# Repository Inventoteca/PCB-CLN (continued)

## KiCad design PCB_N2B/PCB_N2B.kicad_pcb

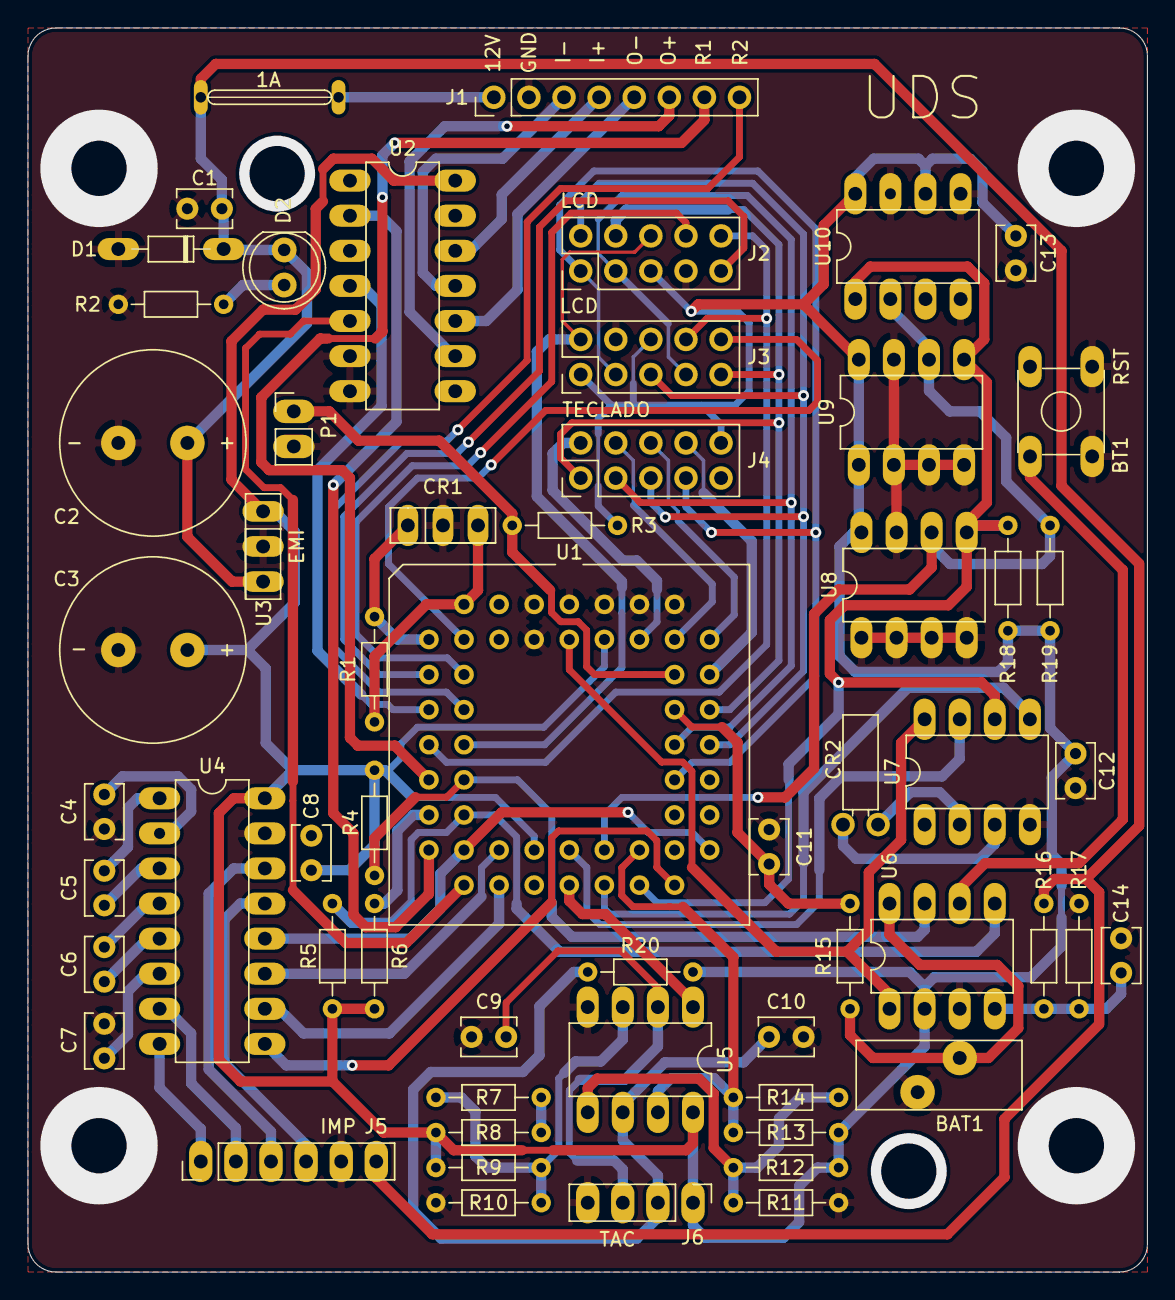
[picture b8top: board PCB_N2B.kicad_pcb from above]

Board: 2 copper layers, 81.0 x 90.0 mm, 58 parts (0 on the bottom side), 71 nets.

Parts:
1A1: Fuse; FUSE_10mm
BAT1: Battery_Cell; BatteryHolder_5.5_5mm
BT1: RST; SW_TH_Tactile_Omron_B3F-10xx
C1, C8, C9, C10, C11, C12, C13, C14: 10nF; C_Disc_D3.8mm_W2.6mm_P2.50mm
C2: 0.22F; CP_13.25_5.0mm
C3: na; CP_13.25_5.0mm
C4, C5, C6, C7: 2,2uF; C_Disc_D3.8mm_W2.6mm_P2.50mm
CR1: 800G137; Crystal_PIN-3
CR2: na; crystal_2.54_8.7mm
D1: na; D_DO-34_SOD68_P7.62mm_Horizontal
D2: RED; LED_D5.0mm_IRBlack
J1: Conn_01x08; PinHeader_1x08_P2.54mm_Vertical
J2, J3: LCD; PinHeader_2x05_P2.54mm_Vertical
J4: Teclado; PinHeader_2x05_P2.54mm_Vertical
J5: IMP; PinHeader_1x06_P2.54mm_Vertical
J6: TAC; PinHeader_1x04_P2.54mm_Vertical
P1: Conn_01x02; PinHeader_1x02_P2.54mm_Vertical
R1, R2, R3, R4, R5, R6, R7, R8, R9, R10, R11, R12, R13, R14, R15, R16, R17, R18, R19, R20: na; R_Axial_DIN0204_L3.6mm_D1.6mm_P7.62mm_Horizontal
U1: 68HC11_PLCC; PLCC-52_THT-Socket
U2: na; DIP-14_W7.62mm
U3: na; Crystal_PIN-3
U4: na; DIP-16_W7.62mm
U5, U6, U7, U8, U9, U10: na; DIP-8_W7.62mm

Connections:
Earth: BAT1.2, BT1.1, BT1.2, C1.2, C2.2, C3.2, C4.1, C7.1, C9.1, C10.2, C11.1, C12.1, C13.1, C14.1, CR1.2, D1.2, J1.2, J2.4, J3.7, J5.5, J6.4, P1.2, R2.1, R10.1, R11.2, R17.1, U1.1, U1.3, U1.4, U1.47, U1.49, U1.51, U2.3, U2.6, U2.7, U3.2, U4.15, U5.4, U6.3, U7.4, U8.1, U8.2, U8.3, U8.4, U8.7, U9.2, U9.3, U9.4, U9.7, U10.4, U10.5, U10.7
unnamed: C1.1, C2.1, D1.1, D2.1, U3.3
unnamed: 1A1.2, J1.1
unnamed: BT1.4, U6.6
unnamed: C9.2, U5.2
unnamed: C10.1, J6.2, R20.1, U5.6
unnamed: C11.2, R15.2, U1.43
unnamed: CR1.1, R1.2
unnamed: CR2.2, U7.2
unnamed: J1.3, U2.11
unnamed: J1.4, U2.12
unnamed: J1.5, U2.10
unnamed: J1.7, U1.16
unnamed: J2.8, J3.6
unnamed: J2.3, J3.1, J3.8, J4.10, R3.2, U9.8, U10.8
unnamed: J4.7, U1.48
unnamed: J4.8, U1.46
unnamed: J5.1, U4.8
unnamed: J5.2, U4.7
unnamed: J5.3, U4.14
unnamed: J5.4, U4.13
unnamed: 1A1.1, J5.6, R16.1
unnamed: D2.2, R2.2
unnamed: P1.1, R3.1, U1.45
unnamed: R4.1, U1.17, U6.7
unnamed: C3.1, C8.1, R4.2, U1.26, U1.52, U2.14, U3.1
unnamed: R5.2, U1.19, U6.5
unnamed: R6.2, U1.18
unnamed: R7.2, R8.2
unnamed: R5.1, R6.1, R8.1, R9.1, U4.16, U5.8
unnamed: R13.1, R14.1, U1.32, U5.7
unnamed: R11.1, R14.2
unnamed: C14.2, R16.2, R17.2, U6.4
unnamed: CR1.3, R1.1, U1.7
unnamed: J3.10, U1.9
unnamed: J2.5, U1.10
unnamed: J2.9, U1.11
unnamed: U1.12, U2.4
unnamed: J1.8, U1.13
unnamed: J2.10, J3.9, U1.14
unnamed: U1.20, U2.2
unnamed: U1.21, U2.5
unnamed: U1.27, U5.1
unnamed: R18.2, U1.31, U7.6, U8.5, U9.5, U10.1
unnamed: J2.1, J3.2, J4.4, U1.39
unnamed: J2.6, J3.3, J4.3, U1.40
unnamed: J2.2, J3.4, J4.2, U1.41
unnamed: J2.7, J3.5, J4.1, U1.42
unnamed: J4.9, U1.44
unnamed: J4.6, U1.50
unnamed: J1.6, U2.9
unnamed: C5.2, U4.1
unnamed: C4.2, U4.2
unnamed: C5.1, U4.3
unnamed: C6.2, U4.4
unnamed: C6.1, U4.5
unnamed: C7.2, U4.6
unnamed: U1.33, U4.9
unnamed: U1.23, U4.10
unnamed: U1.24, U4.11
unnamed: U1.22, U1.34, U4.12
unnamed: R7.1, R9.2, R10.2, U5.3
unnamed: R12.1, U5.5
unnamed: BAT1.1, R15.1, U6.8
unnamed: CR2.1, U7.3
unnamed: U1.29, U7.5
unnamed: U1.28, U7.7
unnamed: U1.2, U6.1, U7.8
unnamed: C12.2, J6.1, R12.2, R13.2, R18.1, R19.1, R20.2, U6.2, U8.8, U9.1
unnamed: R19.2, U1.30, U8.6, U9.6, U10.2
unnamed: C13.2, U10.6

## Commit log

2023-12-15 pcb1
2023-12-15 all pcb
2023-12-16 wip not working yet
